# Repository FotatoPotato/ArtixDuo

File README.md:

# ArtixDuo
 Low cost Dual FPGA Development board featuring two Artix-7 35T Chips, a RP2040 based System Management Controller, Teensy 4.1 MCU and hundreds of user IO for development and testing.

This project is a work in progress.

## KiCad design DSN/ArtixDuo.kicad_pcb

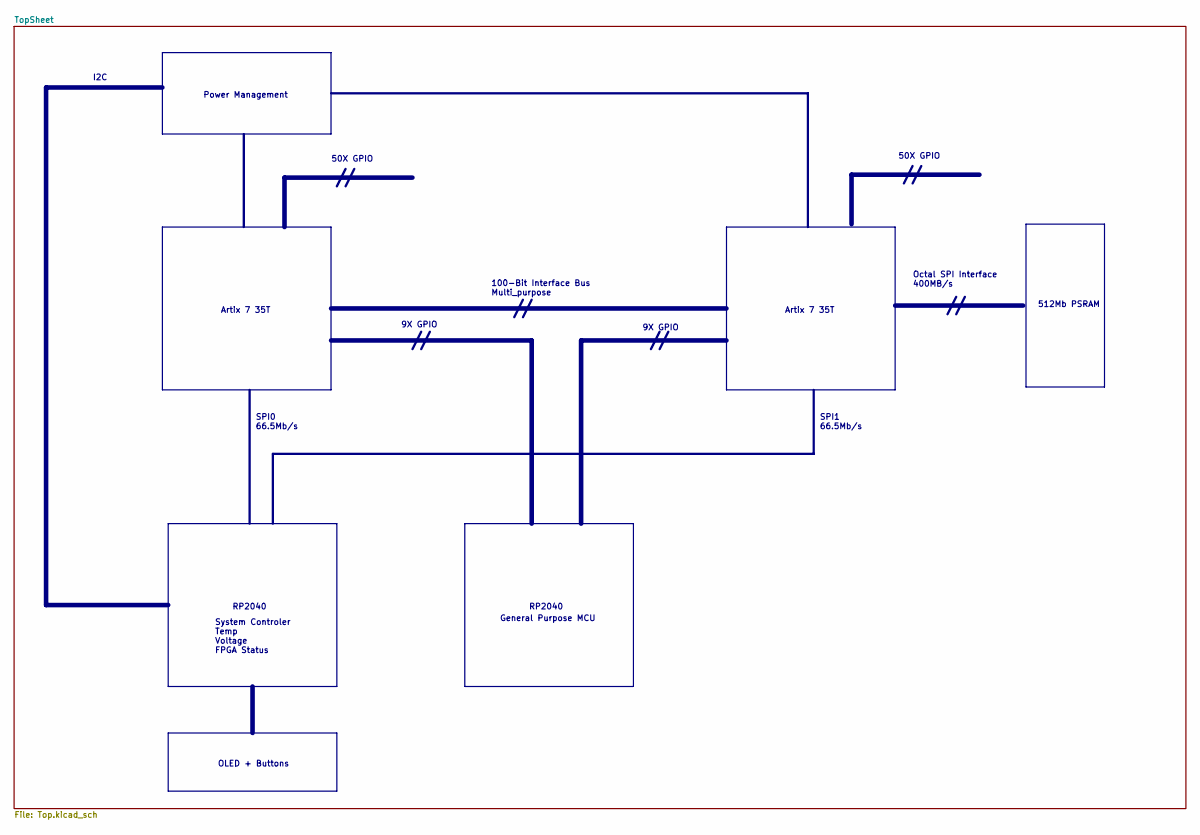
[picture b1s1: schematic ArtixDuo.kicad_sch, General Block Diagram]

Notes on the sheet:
OLED + Buttons
I2C
SPI0 66.5Mb/s
100-Bit Interface Bus Multi_purpose
512Mb PSRAM
Octal SPI Interface 400MB/s
50X GPIO
RP2040
System Controler Temp Voltage FPGA Status
SPI1 66.5Mb/s
Artix 7 35T
Power Management
9X GPIO
General Purpose MCU

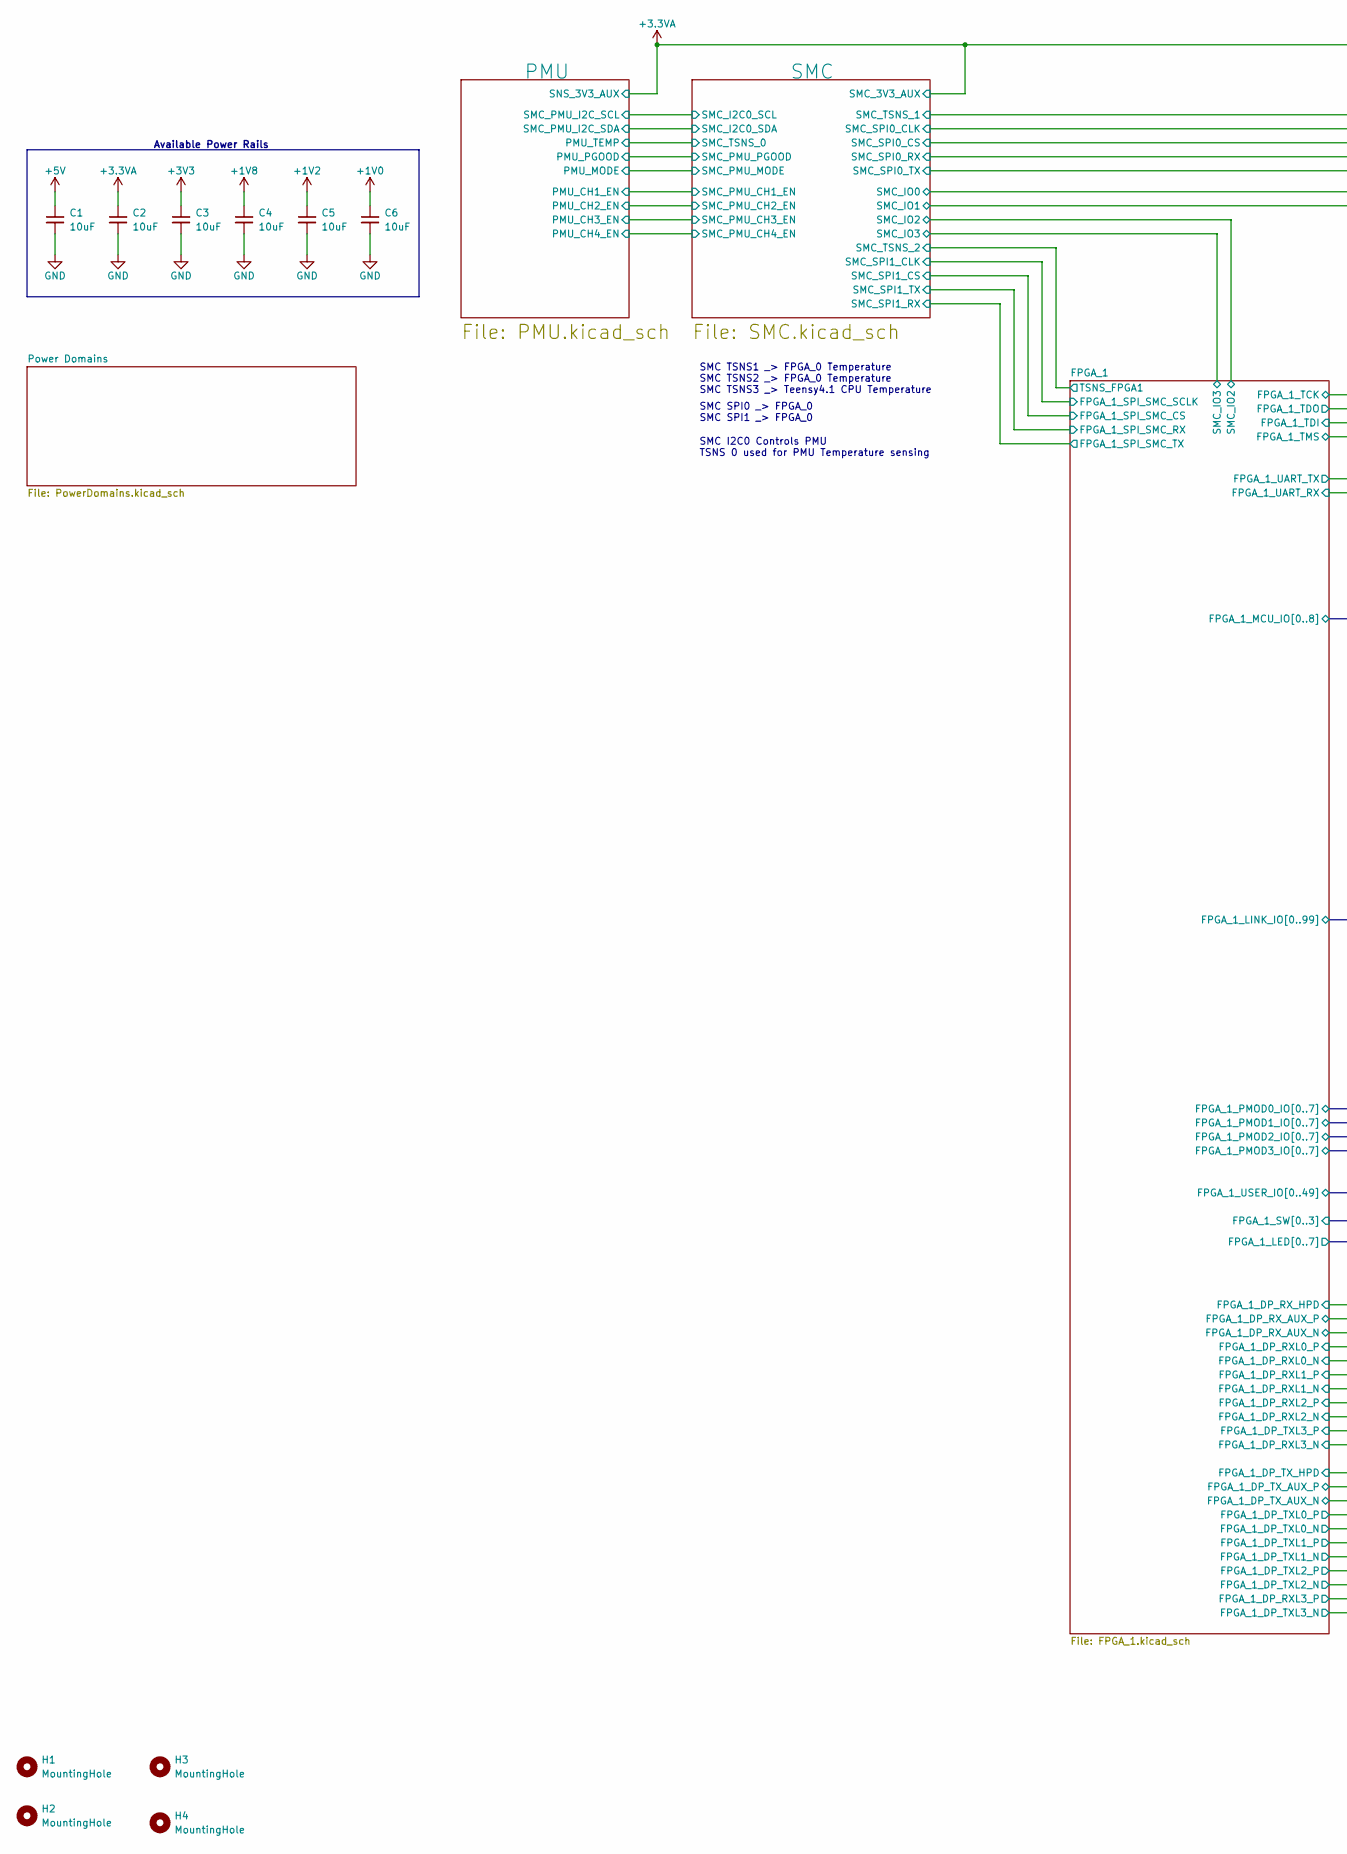
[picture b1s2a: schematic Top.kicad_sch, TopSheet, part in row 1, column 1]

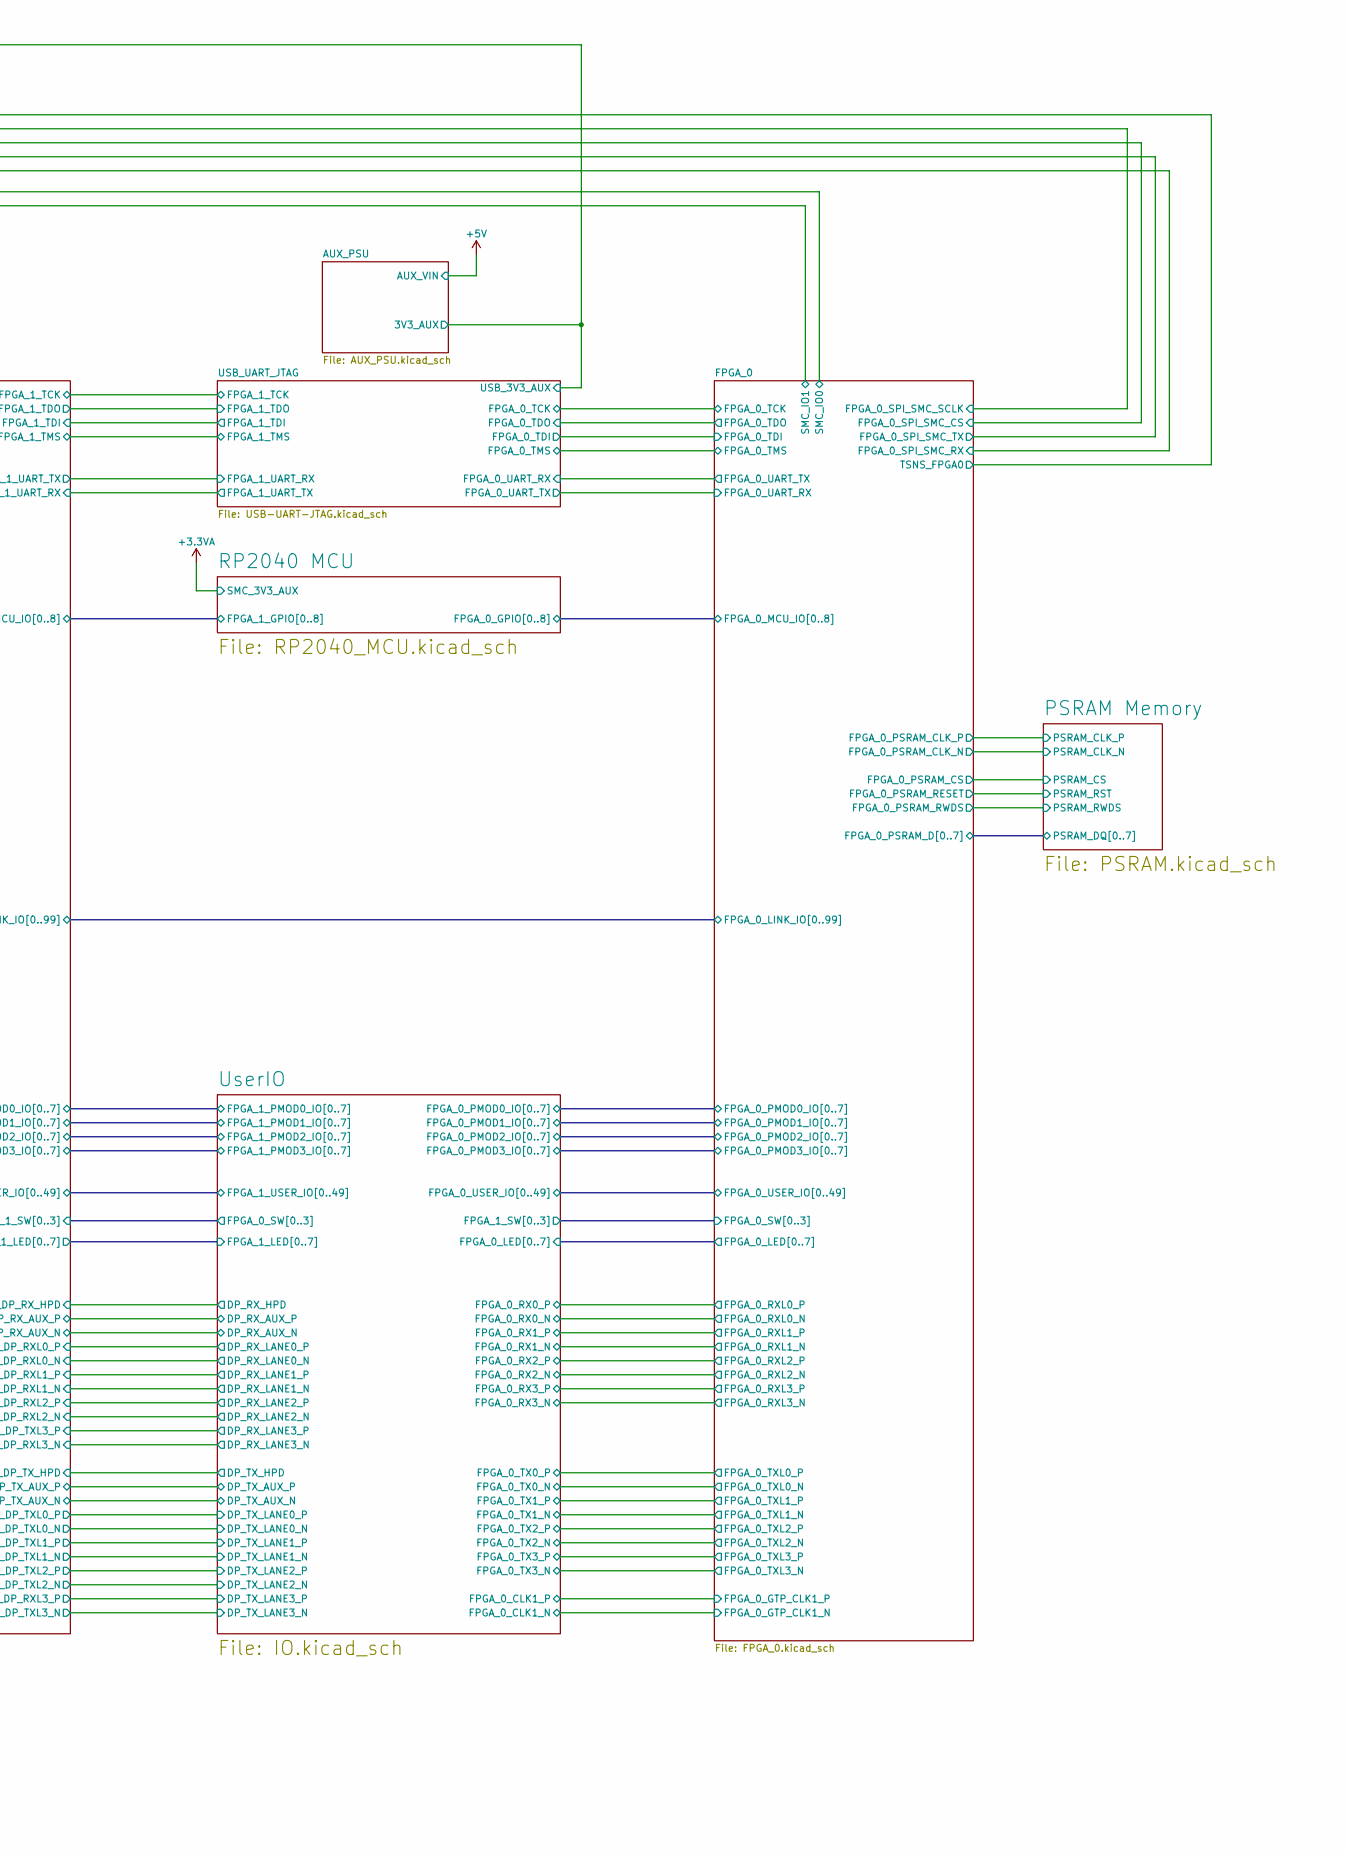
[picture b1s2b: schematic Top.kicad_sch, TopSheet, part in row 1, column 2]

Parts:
C1, C2, C3, C4, C5, C6: 10uF; C_0805_2012Metric; MFR PN GRM21BC71E106KE01K
H1, H2, H3, H4: MountingHole; MountingHole_3.5mm

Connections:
+1V0: C6.1; also elsewhere on the board
+1V2: C5.1; also elsewhere on the board
+1V8: C4.1; also elsewhere on the board
+3.3VA: C2.1; also elsewhere on the board
+3V3: C3.1; also elsewhere on the board

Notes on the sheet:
SMC I2C0 Controls PMU TSNS 0 used for PMU Temperature sensing
Available Power Rails
SMC TSNS1 _> FPGA_0 Temperature SMC TSNS2 _> FPGA_0 Temperature SMC TSNS3 _> Teensy4.1 CPU Temperature
SMC SPI0 _> FPGA_0 SMC SPI1 _> FPGA_0

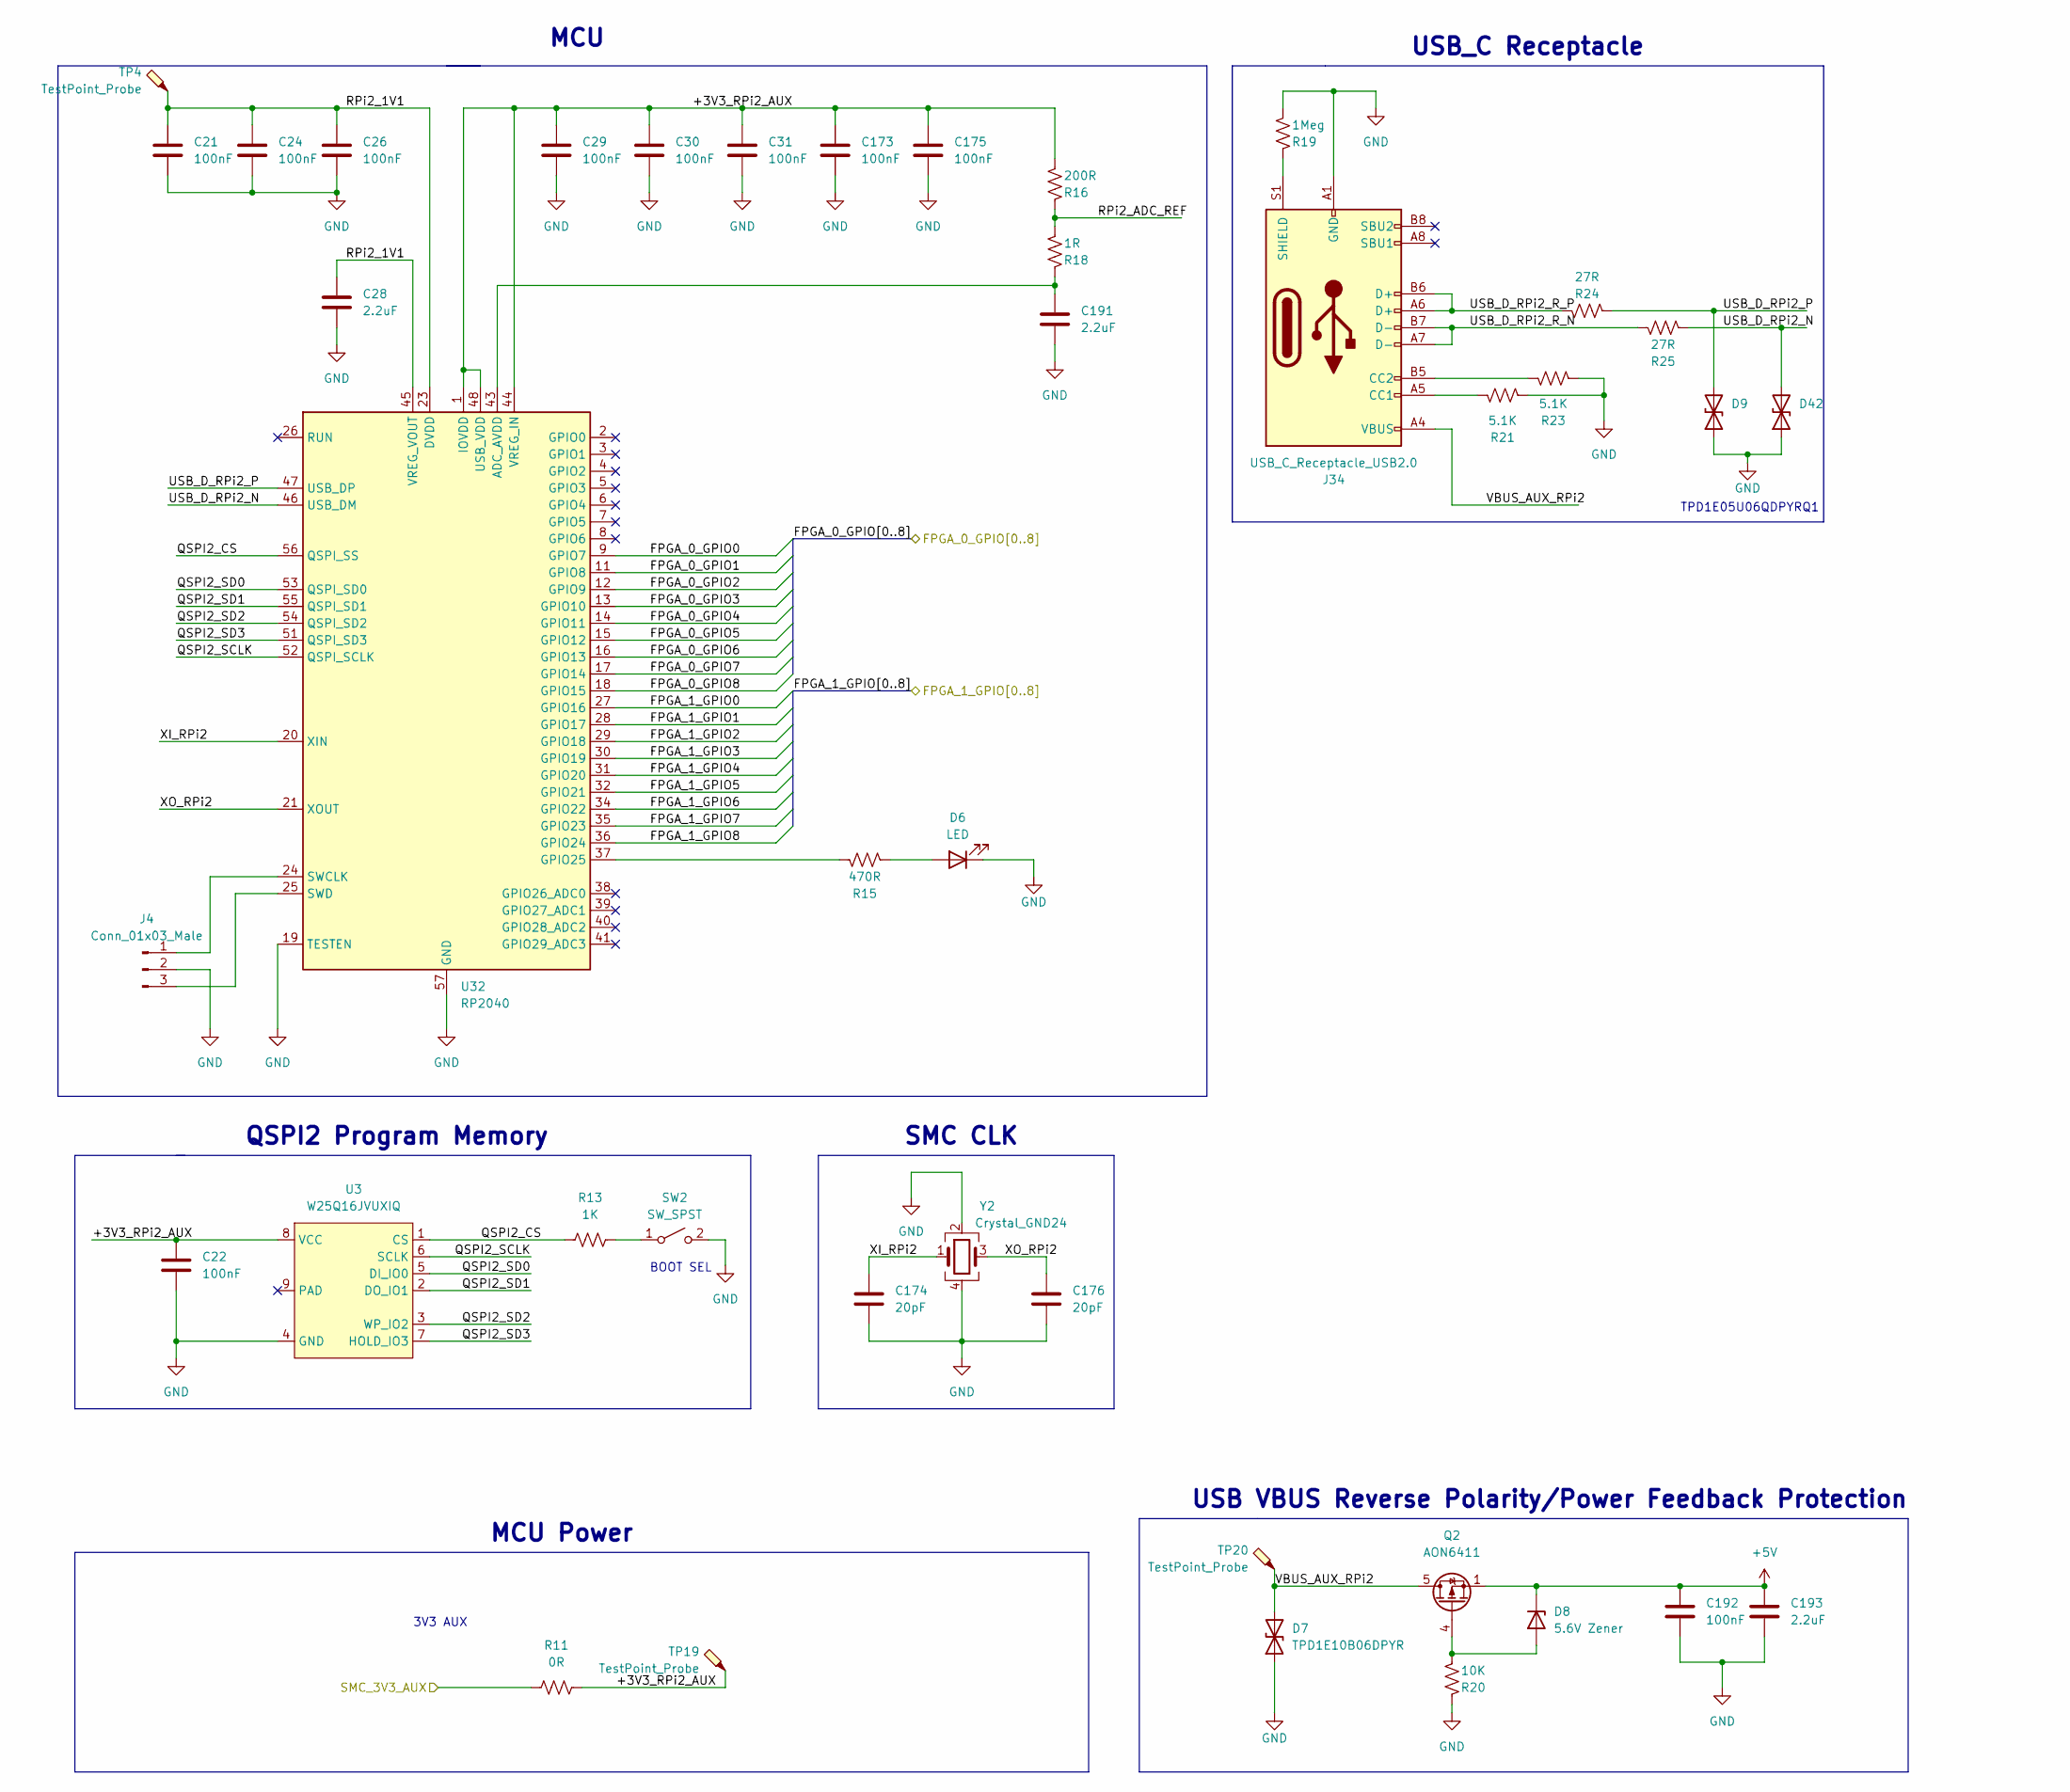
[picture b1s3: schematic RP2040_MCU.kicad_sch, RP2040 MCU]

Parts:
C21, C22, C24, C26, C29, C30, C31, C173, C175, C192: 100nF; C_0402_1005Metric; MFR PN GRM155R71H104ME14J
C28, C191, C193: 2.2uF; C_0402_1005Metric; MFR PN GRT155R61E225KE13D
C174, C176: 20pF; C_0402_1005Metric; MFR PN GCM1555C1H200JA16D
D6: LED; LED_0603_1608Metric; MFR PN B1911PG--20D000514U1930
D7: TPD1E10B06DPYR; D_0402_1005Metric
D8: 5.6V Zener; D_SOD-123; MFR PN MMSZ5232BT1G
D9, D42: TPD1E05U06QDPYRQ1; D_0402_1005Metric
J4: Conn_01x03_Male; PinHeader_1x03_P2.54mm_Vertical
J34: USB_C_Receptacle_USB2.0; USB_C_Receptacle_GCT_USB4085
Q2: AON6411; AO_DFN-8-1EP_5.55x5.2mm_P1.27mm_EP4.12x4.6mm
R11: 0R; R_0402_1005Metric
R13: 1K; R_0402_1005Metric
R15: 470R; R_0402_1005Metric; MFR PN RC0402FR-07470RP
R16: 200R; R_0402_1005Metric; MFR PN RC0402FR-13200RL
R18: 1R; R_0402_1005Metric; MFR PN RC0402FR-071RL
R19: 1Meg; R_0402_1005Metric; MFR PN RC0402FR-071ML
R20: 10K; R_0402_1005Metric; MFR PN RC0402FR-0710KP
R21, R23: 5.1K; R_0402_1005Metric; MFR PN RC0402FR-075K1L
R24, R25: 27R; R_0402_1005Metric; MFR PN RC0402FR-0727RL
SW2: SW_SPST; SW_SPST_B3U-1000P; MFR PN B3U-1000P
TP4, TP19, TP20: TestPoint_Probe; TestPoint_Loop_D1.80mm_Drill1.0mm_Beaded
U3: W25Q16JVUXIQ; WSON-8-1EP_4x4mm_P0.8mm_EP2.2x3mm_ThermalVias; MFR PN W25Q16JVUXIQ TR
U32: RP2040; QFN-56-1EP_7x7mm_P0.4mm_EP3.2x3.2mm
Y2: Crystal_GND24; Crystal_SMD_3225-4Pin_3.2x2.5mm; MFR PN 12M20P2/XT324-10/10

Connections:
+3.3VA: R11.1; also elsewhere on the board
/TopSheet/FPGA_0/FPGA_0_MCU_IO0: U32.9 (GPIO7); also elsewhere on the board
/TopSheet/FPGA_0/FPGA_0_MCU_IO1: U32.11 (GPIO8); also elsewhere on the board
/TopSheet/FPGA_0/FPGA_0_MCU_IO2: U32.12 (GPIO9); also elsewhere on the board
/TopSheet/FPGA_0/FPGA_0_MCU_IO3: U32.13 (GPIO10); also elsewhere on the board
/TopSheet/FPGA_0/FPGA_0_MCU_IO4: U32.14 (GPIO11); also elsewhere on the board
/TopSheet/FPGA_0/FPGA_0_MCU_IO5: U32.15 (GPIO12); also elsewhere on the board
/TopSheet/FPGA_0/FPGA_0_MCU_IO6: U32.16 (GPIO13); also elsewhere on the board
/TopSheet/FPGA_0/FPGA_0_MCU_IO7: U32.17 (GPIO14); also elsewhere on the board
/TopSheet/FPGA_0/FPGA_0_MCU_IO8: U32.18 (GPIO15); also elsewhere on the board
/TopSheet/FPGA_1/FPGA_1_MCU_IO0: U32.27 (GPIO16); also elsewhere on the board
/TopSheet/FPGA_1/FPGA_1_MCU_IO1: U32.28 (GPIO17); also elsewhere on the board
/TopSheet/FPGA_1/FPGA_1_MCU_IO2: U32.29 (GPIO18); also elsewhere on the board
/TopSheet/FPGA_1/FPGA_1_MCU_IO3: U32.30 (GPIO19); also elsewhere on the board
/TopSheet/FPGA_1/FPGA_1_MCU_IO4: U32.31 (GPIO20); also elsewhere on the board
/TopSheet/FPGA_1/FPGA_1_MCU_IO5: U32.32 (GPIO21); also elsewhere on the board
/TopSheet/FPGA_1/FPGA_1_MCU_IO6: U32.34 (GPIO22); also elsewhere on the board
/TopSheet/FPGA_1/FPGA_1_MCU_IO7: U32.35 (GPIO23); also elsewhere on the board
/TopSheet/FPGA_1/FPGA_1_MCU_IO8: U32.36 (GPIO24); also elsewhere on the board
/TopSheet/RP2040 MCU/+3V3_RPi2_AUX: C22.1, C29.1, C30.1, C31.1, C173.1, C175.1, R11.2, R16.1, TP19.1, U3.8 (VCC), U32.1 (IOVDD), U32.10 (IOVDD), U32.22 (IOVDD), U32.33 (IOVDD), U32.42 (IOVDD), U32.44 (VREG_IN), U32.48 (USB_VDD), U32.49 (IOVDD)
/TopSheet/RP2040 MCU/QSPI2_CS: R13.1, U3.1 (CS), U32.56 (QSPI_SS)
/TopSheet/RP2040 MCU/QSPI2_SCLK: U3.6 (SCLK), U32.52 (QSPI_SCLK)
/TopSheet/RP2040 MCU/QSPI2_SD0: U3.5 (DI_IO0), U32.53 (QSPI_SD0)
/TopSheet/RP2040 MCU/QSPI2_SD1: U3.2 (DO_IO1), U32.55 (QSPI_SD1)
/TopSheet/RP2040 MCU/QSPI2_SD2: U3.3 (WP_IO2), U32.54 (QSPI_SD2)
/TopSheet/RP2040 MCU/QSPI2_SD3: U3.7 (HOLD_IO3), U32.51 (QSPI_SD3)
/TopSheet/RP2040 MCU/RPi2_1V1: C21.1, C24.1, C26.1, C28.1, TP4.1, U32.23 (DVDD), U32.45 (VREG_VOUT), U32.50 (DVDD)
/TopSheet/RP2040 MCU/RPi2_ADC_REF: R16.2, R18.1
/TopSheet/RP2040 MCU/USB_D_RPi2_N: D42.2 (A2), R25.2, U32.46 (USB_DM)
/TopSheet/RP2040 MCU/USB_D_RPi2_P: D9.2 (A2), R24.2, U32.47 (USB_DP)
/TopSheet/RP2040 MCU/USB_D_RPi2_R_N: J34.A7 (D-), J34.B7 (D-), R25.1
/TopSheet/RP2040 MCU/USB_D_RPi2_R_P: J34.A6 (D+), J34.B6 (D+), R24.1
/TopSheet/RP2040 MCU/VBUS_AUX_RPi2: D7.2 (A2), J34.A4 (VBUS), J34.A9 (VBUS), J34.B4 (VBUS), J34.B9 (VBUS), Q2.5 (D), TP20.1
/TopSheet/RP2040 MCU/XI_RPi2: C174.1, U32.20 (XIN), Y2.1
/TopSheet/RP2040 MCU/XO_RPi2: C176.1, U32.21 (XOUT), Y2.3
unnamed: C191.1, R18.2, U32.43 (ADC_AVDD)
unnamed: D6.2 (A), R15.2
unnamed: D8.2 (A), Q2.4 (G), R20.1
unnamed: J4.1, U32.24 (SWCLK)
unnamed: J4.3, U32.25 (SWD)
unnamed: J34.A5 (CC1), R21.1
unnamed: J34.B5 (CC2), R23.1
unnamed: J34.S1 (SHIELD), R19.2
unnamed: R13.2, SW2.1 (A)
unnamed: R15.1, U32.37 (GPIO25)

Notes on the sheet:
3V3 AUX
QSPI2 Program Memory
USB_C Receptacle
MCU Power
SMC CLK
USB VBUS Reverse Polarity/Power Feedback Protection
TPD1E05U06QDPYRQ1
MCU
BOOT SEL
